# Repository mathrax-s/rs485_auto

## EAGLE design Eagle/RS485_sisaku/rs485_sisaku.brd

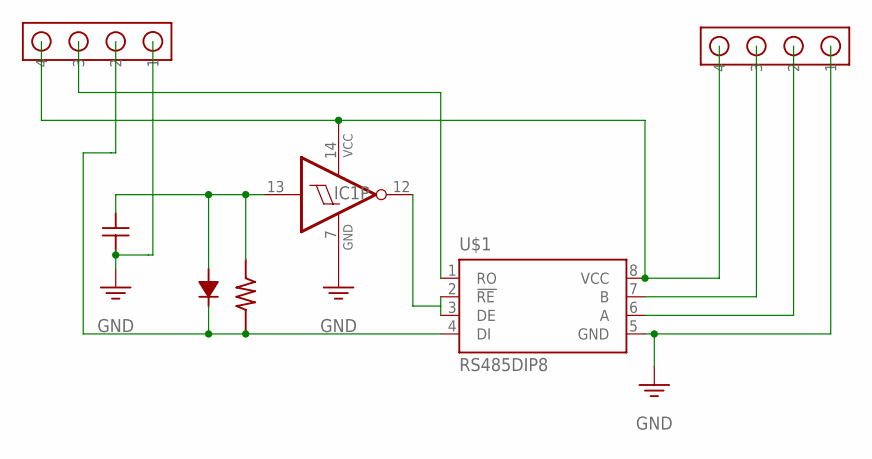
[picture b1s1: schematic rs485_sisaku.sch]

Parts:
IC1: 7414N; DIL14
U$1: RS485DIP8; DIP826W53P254L959H508Q8B
U$2: RESISTOR; RESISTOR-1/4W
U$3: DIODE-S
U$5: CAPACITOR-CEL; 100NF
U$8, U$9: EH4

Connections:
GND: IC1.7 (GND), U$1.5 (GND), U$5.1, U$8.1, U$9.1
unnamed: IC1.12 (O), U$1.2 (RE), U$1.3 (DE)
unnamed: IC1.13 (I), U$2.P$2, U$3.1, U$5.2
unnamed: IC1.14 (VCC), U$1.8 (VCC), U$8.4, U$9.4
unnamed: U$1.4 (DI), U$2.P$1, U$3.2, U$8.2
unnamed: U$1.1 (RO), U$8.3
unnamed: U$1.7 (B), U$9.3
unnamed: U$1.6 (A), U$9.2

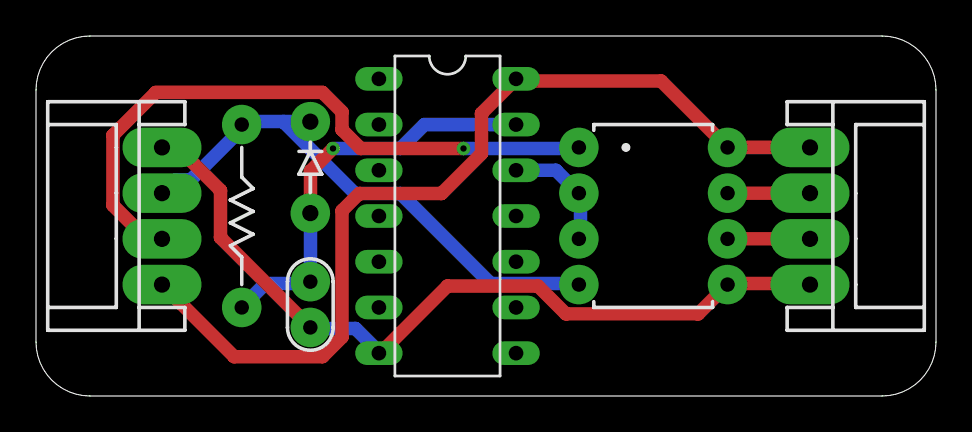
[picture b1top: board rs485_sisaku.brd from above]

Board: 2 copper layers, 50.0 x 20.0 mm, 7 parts (0 on the bottom side), 8 nets.

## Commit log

2022-06-30 2022_0630
